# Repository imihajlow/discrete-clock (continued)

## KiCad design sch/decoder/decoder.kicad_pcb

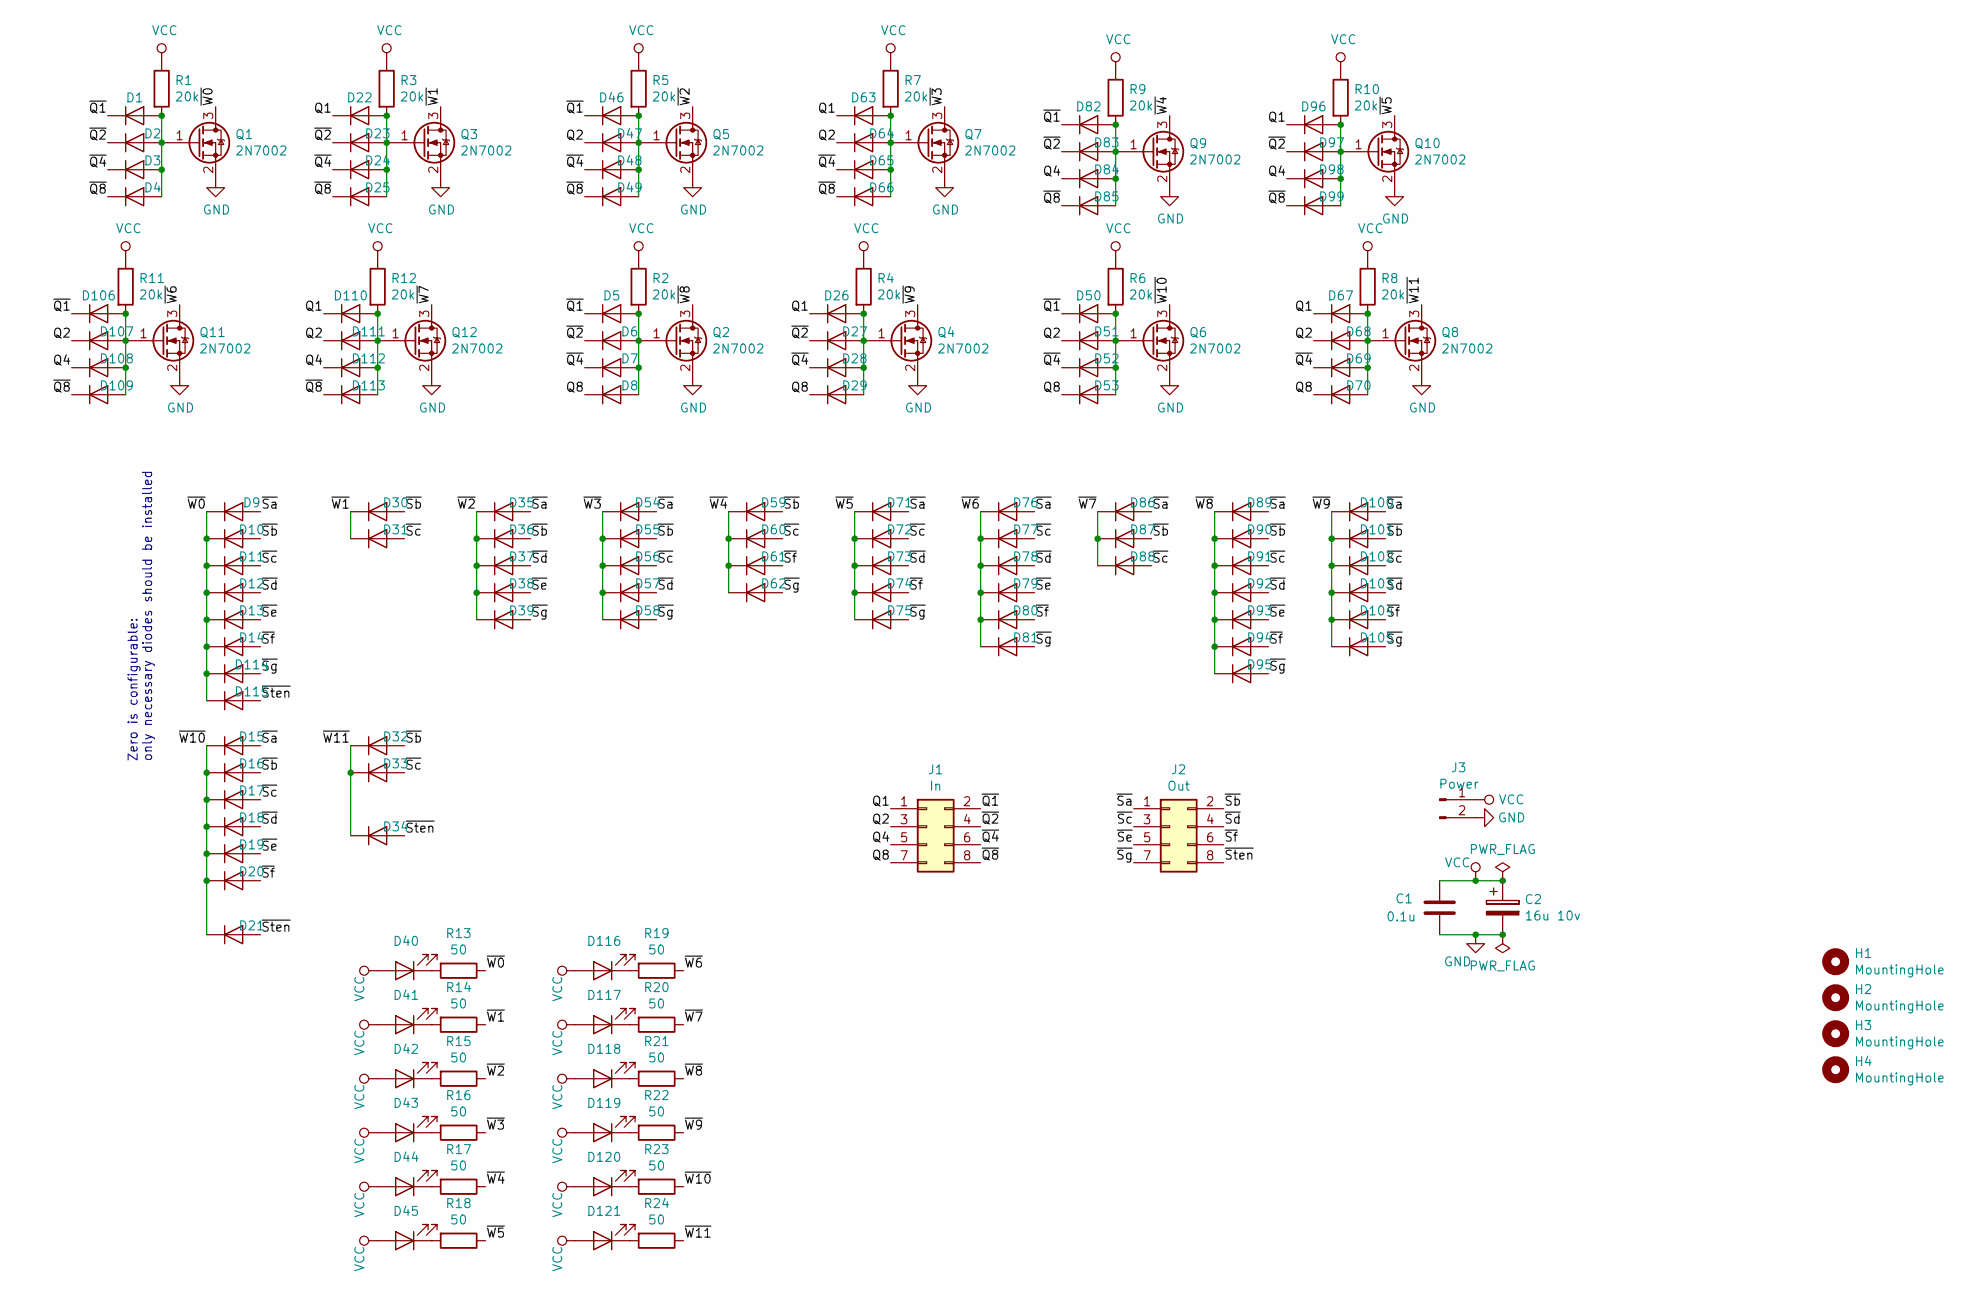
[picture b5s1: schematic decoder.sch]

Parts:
C1: 0.1u; C_0805_2012Metric
C2: 16u 10v; CP_EIA-3528-21_Kemet-B
D1, D2, D3, D4, D5, D6, D7, D8, D9, D10, D11, D12, D13, D14, D15, D16, D17, D18, D19, D20, D21, D22, D23, D24, D25, D26, D27, D28, D29, D30, D31, D32, D33, D34, D35, D36, D37, D38, D39, D46, D47, D48, D49, D50, D51, D52, D53, D54, D55, D56, D57, D58, D59, D60, D61, D62, D63, D64, D65, D66, D67, D68, D69, D70, D71, D72, D73, D74, D75, D76, D77, D78, D79, D80, D81, D82, D83, D84, D85, D86, D87, D88, D89, D90, D91, D92, D93, D94, D95, D96, D97, D98, D99, D100, D101, D102, D103, D104, D105, D106, D107, D108, D109, D110, D111, D112, D113, D114, D115: D; D_MiniMELF
D40, D41, D42, D43, D44, D45, D116, D117, D118, D119, D120, D121: LED; LED_0805_2012Metric
H1, H2, H3, H4: MountingHole; MountingHole_3.2mm_M3_DIN965_Pad
J1: In; IDC-Header_2x04_P2.54mm_Vertical
J2: Out; IDC-Header_2x04_P2.54mm_Vertical
J3: Power; PinHeader_1x02_P2.54mm_Vertical
Q1, Q2, Q3, Q4, Q5, Q6, Q7, Q8, Q9, Q10, Q11, Q12: 2N7002; SOT-23
R1, R2, R3, R4, R5, R6, R7, R8, R9, R10, R11, R12: 20k; R_0805_2012Metric
R13, R14, R15, R16, R17, R18, R19, R20, R21, R22, R23, R24: 50; R_0805_2012Metric

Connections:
/Q1: D22.1 (K), D26.1 (K), D63.1 (K), D67.1 (K), D96.1 (K), D110.1 (K), J1.1
/Q2: D47.1 (K), D51.1 (K), D64.1 (K), D68.1 (K), D107.1 (K), D111.1 (K), J1.3
/Q4: D84.1 (K), D98.1 (K), D108.1 (K), D112.1 (K), J1.5
/Q8: D8.1 (K), D29.1 (K), D53.1 (K), D70.1 (K), J1.7
/~Q1: D1.1 (K), D5.1 (K), D46.1 (K), D50.1 (K), D82.1 (K), D106.1 (K), J1.2
/~Q2: D2.1 (K), D6.1 (K), D23.1 (K), D27.1 (K), D83.1 (K), D97.1 (K), J1.4
/~Q4: D3.1 (K), D7.1 (K), D24.1 (K), D28.1 (K), D48.1 (K), D52.1 (K), D65.1 (K), D69.1 (K), J1.6
/~Q8: D4.1 (K), D25.1 (K), D49.1 (K), D66.1 (K), D85.1 (K), D99.1 (K), D109.1 (K), D113.1 (K), J1.8
/~Sa: D9.2 (A), D15.2 (A), D35.2 (A), D54.2 (A), D71.2 (A), D76.2 (A), D86.2 (A), D89.2 (A), D100.2 (A), J2.1
/~Sb: D10.2 (A), D16.2 (A), D30.2 (A), D32.2 (A), D36.2 (A), D55.2 (A), D59.2 (A), D87.2 (A), D90.2 (A), D101.2 (A), J2.2
/~Sc: D11.2 (A), D17.2 (A), D31.2 (A), D33.2 (A), D56.2 (A), D60.2 (A), D72.2 (A), D77.2 (A), D88.2 (A), D91.2 (A), D102.2 (A), J2.3
/~Sd: D12.2 (A), D18.2 (A), D37.2 (A), D57.2 (A), D73.2 (A), D78.2 (A), D92.2 (A), D103.2 (A), J2.4
/~Se: D13.2 (A), D19.2 (A), D38.2 (A), D79.2 (A), D93.2 (A), J2.5
/~Sf: D14.2 (A), D20.2 (A), D61.2 (A), D74.2 (A), D80.2 (A), D94.2 (A), D104.2 (A), J2.6
/~Sg: D39.2 (A), D58.2 (A), D62.2 (A), D75.2 (A), D81.2 (A), D95.2 (A), D105.2 (A), D114.2 (A), J2.7
/~Sten: D21.2 (A), D34.2 (A), D115.2 (A), J2.8
/~W0: D9.1 (K), D10.1 (K), D11.1 (K), D12.1 (K), D13.1 (K), D14.1 (K), D114.1 (K), D115.1 (K), Q1.3 (D), R13.1
/~W1: D30.1 (K), D31.1 (K), Q3.3 (D), R14.1
/~W2: D35.1 (K), D36.1 (K), D37.1 (K), D38.1 (K), D39.1 (K), Q5.3 (D), R15.1
/~W3: D54.1 (K), D55.1 (K), D56.1 (K), D57.1 (K), D58.1 (K), Q7.3 (D), R16.1
/~W4: D59.1 (K), D60.1 (K), D61.1 (K), D62.1 (K), Q9.3 (D), R17.1
/~W5: D71.1 (K), D72.1 (K), D73.1 (K), D74.1 (K), D75.1 (K), Q10.3 (D), R18.1
/~W6: D76.1 (K), D77.1 (K), D78.1 (K), D79.1 (K), D80.1 (K), D81.1 (K), Q11.3 (D), R19.1
/~W7: D86.1 (K), D87.1 (K), D88.1 (K), Q12.3 (D), R20.1
/~W8: D89.1 (K), D90.1 (K), D91.1 (K), D92.1 (K), D93.1 (K), D94.1 (K), D95.1 (K), Q2.3 (D), R21.1
/~W9: D100.1 (K), D101.1 (K), D102.1 (K), D103.1 (K), D104.1 (K), D105.1 (K), Q4.3 (D), R22.1
/~W10: D15.1 (K), D16.1 (K), D17.1 (K), D18.1 (K), D19.1 (K), D20.1 (K), D21.1 (K), Q6.3 (D), R23.1
/~W11: D32.1 (K), D33.1 (K), D34.1 (K), Q8.3 (D), R24.1
GND: C1.2, C2.2, J3.2, Q1.2 (S), Q2.2 (S), Q3.2 (S), Q4.2 (S), Q5.2 (S), Q6.2 (S), Q7.2 (S), Q8.2 (S), Q9.2 (S), Q10.2 (S), Q11.2 (S), Q12.2 (S)
unnamed: D1.2 (A), D2.2 (A), D3.2 (A), D4.2 (A), Q1.1 (G), R1.2
unnamed: D5.2 (A), D6.2 (A), D7.2 (A), D8.2 (A), Q2.1 (G), R2.2
unnamed: D22.2 (A), D23.2 (A), D24.2 (A), D25.2 (A), Q3.1 (G), R3.2
unnamed: D26.2 (A), D27.2 (A), D28.2 (A), D29.2 (A), Q4.1 (G), R4.2
unnamed: D40.1 (K), R13.2
unnamed: D41.1 (K), R14.2
unnamed: D42.1 (K), R15.2
unnamed: D43.1 (K), R16.2
unnamed: D44.1 (K), R17.2
unnamed: D45.1 (K), R18.2
unnamed: D46.2 (A), D47.2 (A), D48.2 (A), D49.2 (A), Q5.1 (G), R5.2
unnamed: D50.2 (A), D51.2 (A), D52.2 (A), D53.2 (A), Q6.1 (G), R6.2
unnamed: D63.2 (A), D64.2 (A), D65.2 (A), D66.2 (A), Q7.1 (G), R7.2
unnamed: D67.2 (A), D68.2 (A), D69.2 (A), D70.2 (A), Q8.1 (G), R8.2
unnamed: D82.2 (A), D83.2 (A), D84.2 (A), D85.2 (A), Q9.1 (G), R9.2
unnamed: D96.2 (A), D97.2 (A), D98.2 (A), D99.2 (A), Q10.1 (G), R10.2
unnamed: D106.2 (A), D107.2 (A), D108.2 (A), D109.2 (A), Q11.1 (G), R11.2
unnamed: D110.2 (A), D111.2 (A), D112.2 (A), D113.2 (A), Q12.1 (G), R12.2
unnamed: D116.1 (K), R19.2
unnamed: D117.1 (K), R20.2
unnamed: D118.1 (K), R21.2
unnamed: D119.1 (K), R22.2
unnamed: D120.1 (K), R23.2
unnamed: D121.1 (K), R24.2
VCC: C1.1, C2.1, D40.2 (A), D41.2 (A), D42.2 (A), D43.2 (A), D44.2 (A), D45.2 (A), D116.2 (A), D117.2 (A), D118.2 (A), D119.2 (A), D120.2 (A), D121.2 (A), J3.1, R1.1, R2.1, R3.1, R4.1, R5.1, R6.1, R7.1, R8.1, R9.1, R10.1, R11.1, R12.1

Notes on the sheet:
Zero is configurable: only necessary diodes should be installed

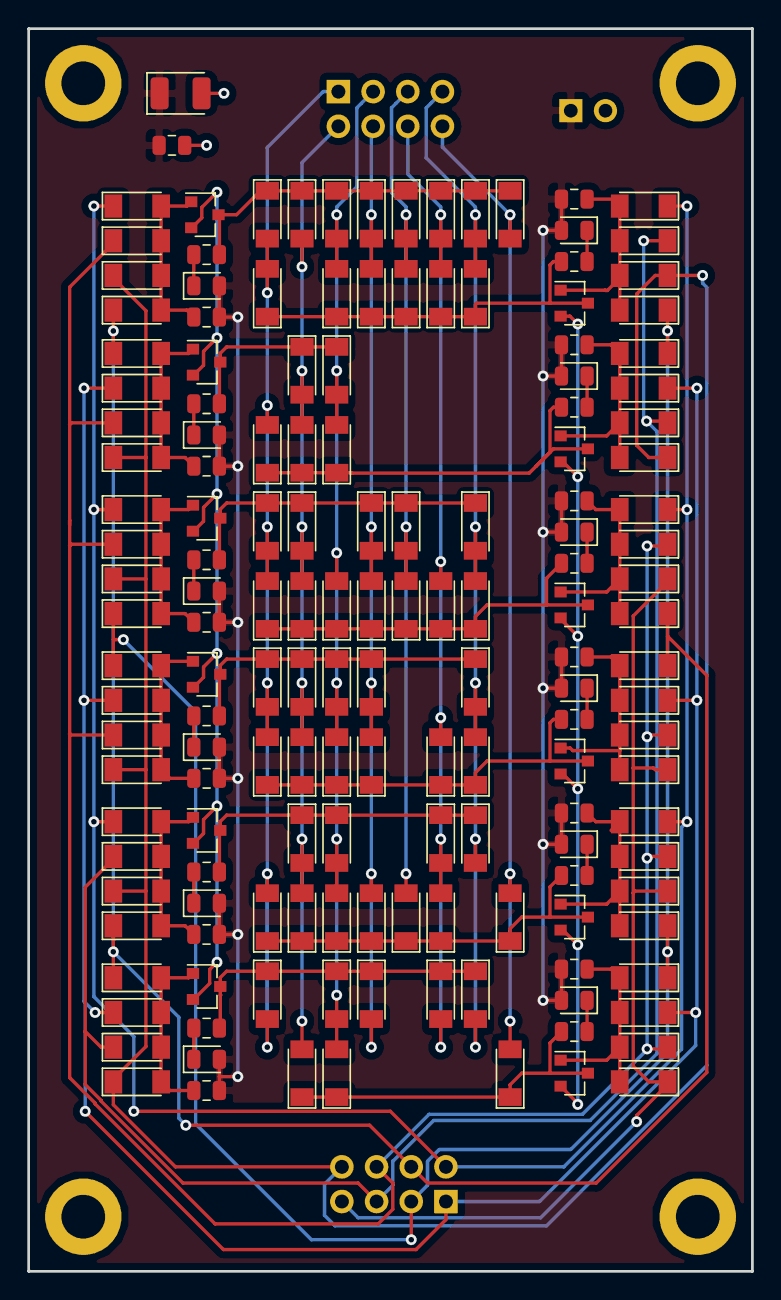
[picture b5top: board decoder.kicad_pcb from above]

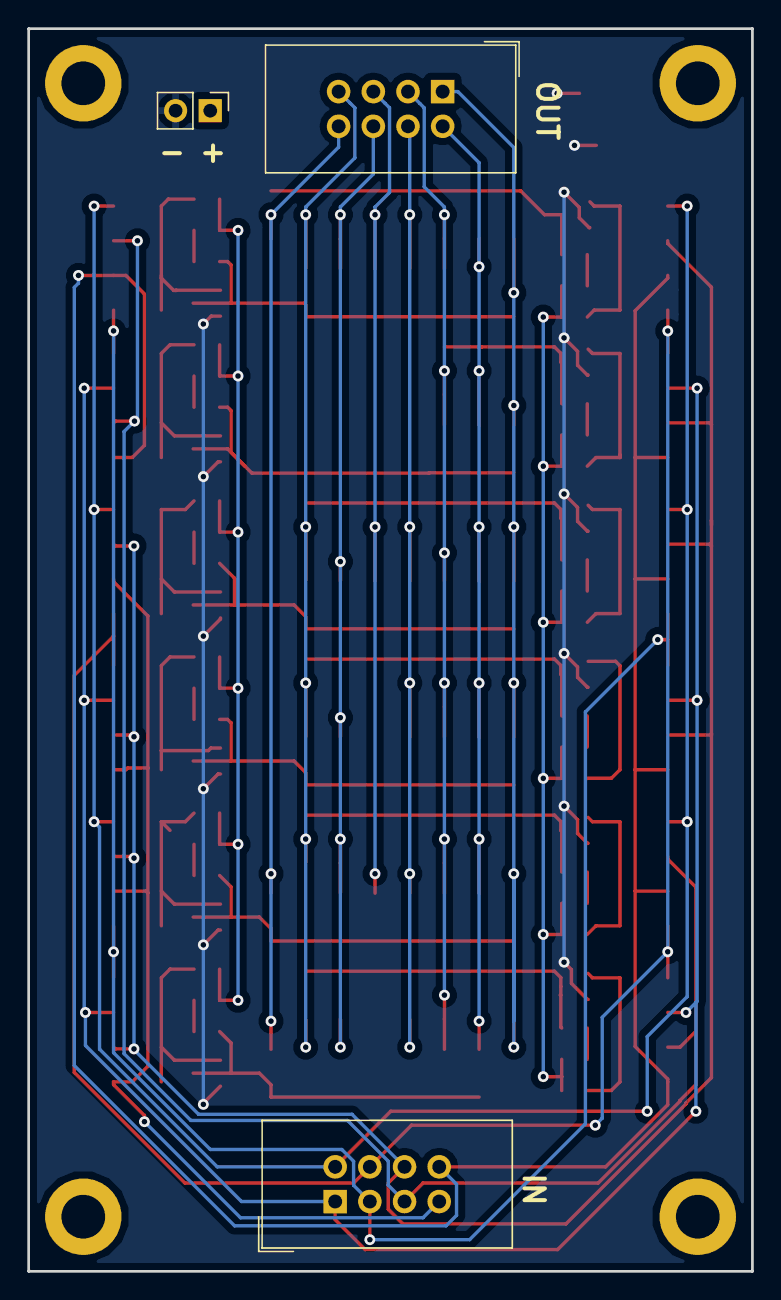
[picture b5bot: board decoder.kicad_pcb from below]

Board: 2 copper layers, 53.0 x 91.0 mm, 166 parts (3 on the bottom side), 54 nets.

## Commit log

2018-11-17 Models added
    A working flip-flop with sync and async reset
2018-11-20 Working diode-nmos flip-flop simulation
2018-11-20 Resistance parameter
    The higher the resistance the higher the stability
2018-11-24 Counter schematic added
2018-11-24 Counter schematic improvements
2018-11-24 Counter model
2018-11-24 Removed unneed file
2018-11-27 One flip-flop is placed on PCB
2018-11-30 The counter board is complete
2018-12-01 Removed unused jumpers
2018-12-03 Board modified: connectors used
2018-12-04 Decoder scematic added
2018-12-06 Decoder board added
    Also schematics modified: added LEDs, configurable zero
2018-12-07 Decoder board finished
2018-12-07 Modified the counter board
    Added mounting holes to the schematics
    Changed reset connector to have 2 pins
    Added labels for connectors and configuration diodes
2018-12-10 A XOR module is added to the counter model
2018-12-10 7-seg decoder model
2018-12-15 Added display board schematics and reset model
2018-12-15 Total consumption summary
2018-12-17 7-segment indicator footprint is added
2018-12-18 Button footprint added
2019-01-04 Power supply schematic and clock generation model
2019-01-06 Added datasheets, set component values, calculated LED resistors
2019-01-09 Added bill of materials, modified counter PCB
    Adjusted component positions for better GND filling
2019-01-12 Display board, BOM updated
2019-01-13 Power supply board
2019-01-13 Display module board
2019-01-13 Deleted some models
